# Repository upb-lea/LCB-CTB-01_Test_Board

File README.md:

# Test board LCB-CTB-01 for the LEA control board

This is the test board for the LEA control board LCB-CCB-01. It is used for testing an LCB-board to see if this works well. Please refer to the [LCB-CCB-01 repository](https://github.com/upb-lea/LCB-CCB-01_LEA_Control_Board) for a PCB and project overview.

Note, that you also need to install the `LEA KiCad Library` to view this PCB in this repository. To do this, follow the instructions mentioned [here](https://github.com/upb-lea/LCB-CCB-01_LEA_Control_Board/blob/main/README.md#downloading-this-project-and-folder-structure).

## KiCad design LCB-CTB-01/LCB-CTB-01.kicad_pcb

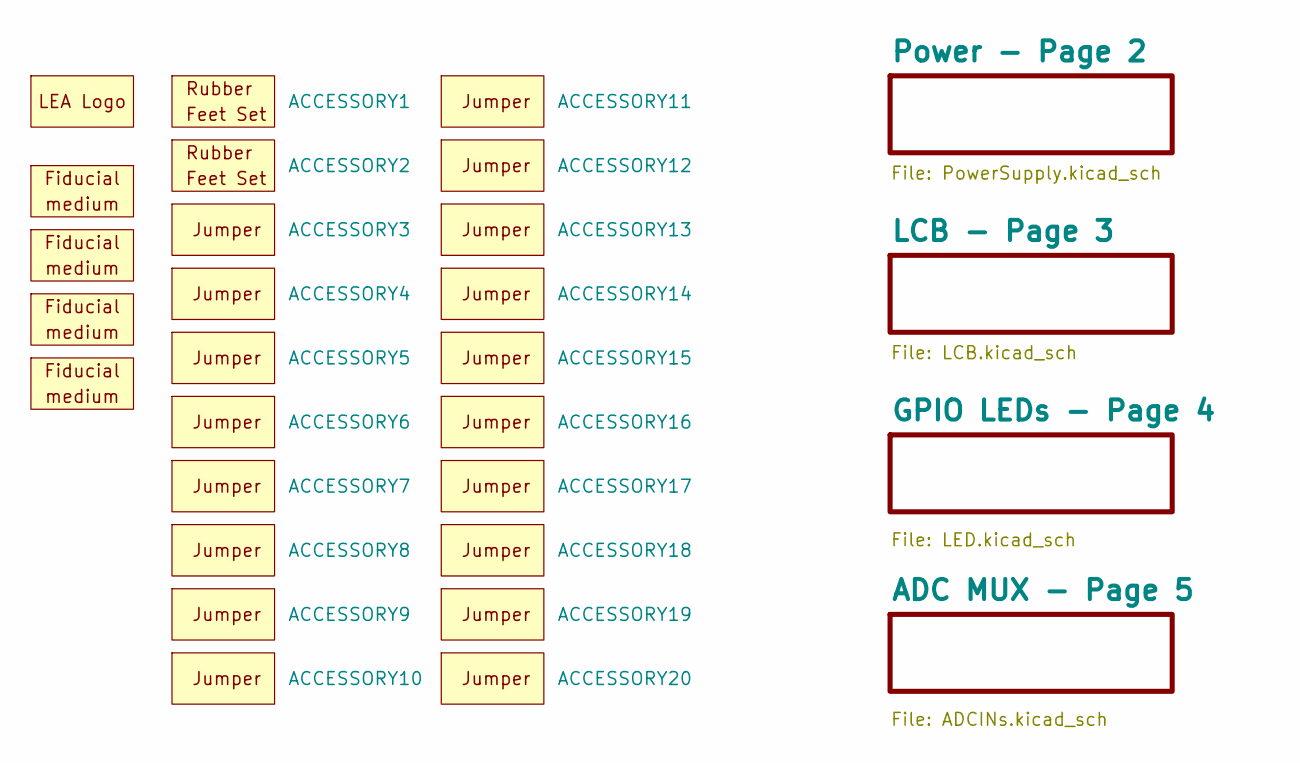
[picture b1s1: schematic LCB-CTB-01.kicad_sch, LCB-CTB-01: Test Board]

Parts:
ACCESSORY1, ACCESSORY2: ACCESSORY_rubber_feet; mouser# 485-550
ACCESSORY3, ACCESSORY4, ACCESSORY5, ACCESSORY6, ACCESSORY7, ACCESSORY8, ACCESSORY9, ACCESSORY10, ACCESSORY11, ACCESSORY12, ACCESSORY13, ACCESSORY14, ACCESSORY15, ACCESSORY16, ACCESSORY17, ACCESSORY18, ACCESSORY19, ACCESSORY20: ACCESSORY_jumper; mouser# 571-8815451
O1: SYM_LEA_Logo; SYM_lea_logo
O2, O3, O4, O5: Fiducial_medium; Fiducials_medium

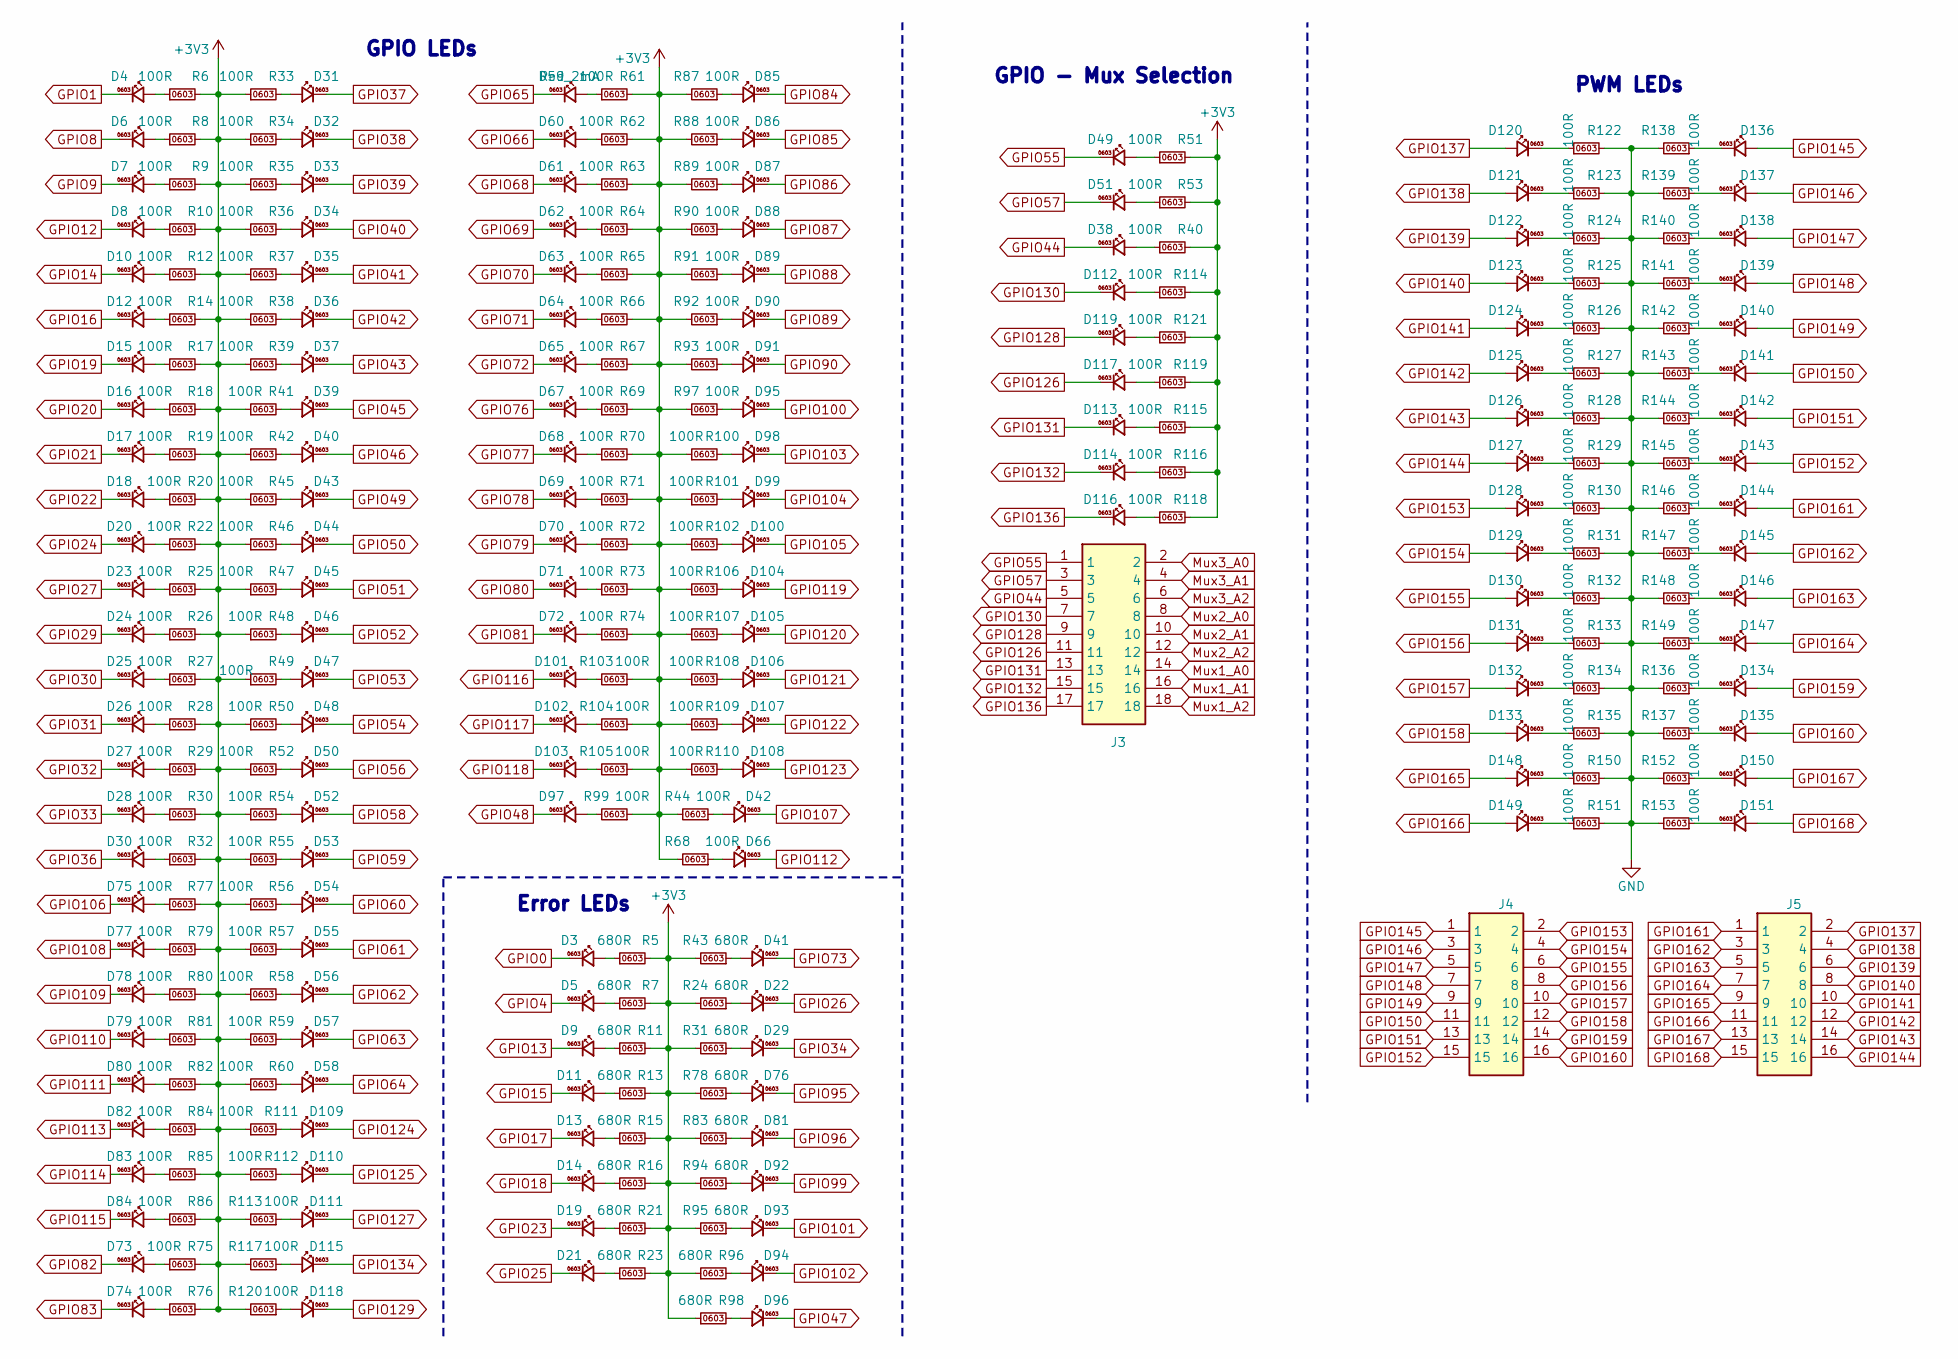
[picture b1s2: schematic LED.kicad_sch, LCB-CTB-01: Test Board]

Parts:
D3, D5, D9, D11, D13, D14, D19, D21, D22, D29, D41, D59, D76, D81, D92, D93, D94, D96: Red_2mA; LED_0603; mouser# 604-APHD1608LSURCK
D4, D6, D7, D8, D10, D12, D15, D16, D17, D18, D20, D23, D24, D25, D26, D27, D28, D30, D31, D32, D33, D34, D35, D36, D37, D38, D39, D40, D42, D43, D44, D45, D46, D47, D48, D49, D50, D51, D52, D53, D54, D55, D56, D57, D58, D60, D61, D62, D63, D64, D65, D66, D67, D68, D69, D70, D71, D72, D73, D74, D75, D77, D78, D79, D80, D82, D83, D84, D85, D86, D87, D88, D89, D90, D91, D95, D97, D98, D99, D100, D101, D102, D103, D104, D105, D106, D107, D108, D109, D110, D111, D112, D113, D114, D115, D116, D117, D118, D119, D120, D121, D122, D123, D124, D125, D126, D127, D128, D129, D130, D131, D132, D133, D134, D135, D136, D137, D138, D139, D140, D141, D142, D143, D144, D145, D146, D147, D148, D149, D150, D151: LED_0603_BLUE; LED_0603; mouser# 604-APHD1608LVBCD
J3: Conn_02x09_Male; mouser# 855-M20-9980946
J4, J5: Conn_02x08_Male; HDRV16W64P254_2X8_2032X508X914P; mouser# 855-M20-9980846
R5, R7, R11, R13, R15, R16, R21, R23, R24, R31, R43, R78, R83, R94, R95, R96, R98: 680R; R_0603; mouser# 71-CRCW0603680RFKEAC
R6, R8, R9, R10, R12, R14, R17, R18, R19, R20, R22, R25, R26, R27, R28, R29, R30, R32, R33, R34, R35, R36, R37, R38, R39, R40, R41, R42, R44, R45, R46, R47, R48, R49, R50, R51, R52, R53, R54, R55, R56, R57, R58, R59, R60, R61, R62, R63, R64, R65, R66, R67, R68, R69, R70, R71, R72, R73, R74, R75, R76, R77, R79, R80, R81, R82, R84, R85, R86, R87, R88, R89, R90, R91, R92, R93, R97, R99, R100, R101, R102, R103, R104, R105, R106, R107, R108, R109, R110, R111, R112, R113, R114, R115, R116, R117, R118, R119, R120, R121, R122, R123, R124, R125, R126, R127, R128, R129, R130, R131, R132, R133, R134, R135, R136, R137, R138, R139, R140, R141, R142, R143, R144, R145, R146, R147, R148, R149, R150, R151, R152, R153: 100R; R_0603; mouser# 71-CRCW0603100RFKEAC

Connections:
+3V3: R5.2, R6.2, R7.2, R8.2, R9.2, R10.2, R11.2, R12.2, R13.2, R14.2, R15.2, R16.2, R17.2, R18.2, R19.2, R20.2, R21.2, R22.2, R23.2, R24.2, R25.2, R26.2, R27.2, R28.2, R29.2, R30.2, R31.2, R32.2, R33.1, R34.1, R35.1, R36.1, R37.1, R38.1, R39.1, R40.2, R41.1, R42.1, R43.2, R44.2, R45.1, R46.1, R47.1, R48.1, R49.1, R50.1, R51.2, R52.1, R53.2, R54.1, R55.1, R56.1, R57.1, R58.1, R59.1, R60.1, R61.2, R62.2, R63.2, R64.2, R65.2, R66.2, R67.2, R68.2, R69.2, R70.2, R71.2, R72.2, R73.2, R74.2, R75.2, R76.2, R77.2, R78.2, R79.2, R80.2, R81.2, R82.2, R83.2, R84.2, R85.2, R86.2, R87.2, R88.2, R89.2, R90.2, R91.2, R92.2, R93.2, R94.2, R95.2, R96.1, R97.2, R98.1, R99.1, R100.1, R101.1, R102.1, R103.1, R104.1, R105.1, R106.1, R107.1, R108.1, R109.1, R110.1, R111.1, R112.1, R113.2, R114.2, R115.2, R116.2, R117.2, R118.2, R119.2, R120.2, R121.2; also elsewhere on the board
GND: R122.2, R123.2, R124.2, R125.2, R126.2, R127.2, R128.2, R129.2, R130.2, R131.2, R132.2, R133.2, R134.2, R135.2, R136.2, R137.2, R138.2, R139.2, R140.2, R141.2, R142.2, R143.2, R144.2, R145.2, R146.2, R147.2, R148.2, R149.2, R150.2, R151.2, R152.2, R153.2; also elsewhere on the board
GPIO0: D3.C; also elsewhere on the board
GPIO1: D4.C; also elsewhere on the board
GPIO4: D5.C; also elsewhere on the board
GPIO8: D6.C; also elsewhere on the board
GPIO9: D7.C; also elsewhere on the board
GPIO12: D8.C; also elsewhere on the board
GPIO13: D9.C; also elsewhere on the board
GPIO14: D10.C; also elsewhere on the board
GPIO15: D11.C; also elsewhere on the board
GPIO16: D12.C; also elsewhere on the board
GPIO17: D13.C; also elsewhere on the board
GPIO18: D14.C; also elsewhere on the board
GPIO19: D15.C; also elsewhere on the board
GPIO20: D16.C; also elsewhere on the board
GPIO21: D17.C; also elsewhere on the board
GPIO22: D18.C; also elsewhere on the board
GPIO23: D19.C; also elsewhere on the board
GPIO24: D20.C; also elsewhere on the board
GPIO25: D21.C; also elsewhere on the board
GPIO26: D22.C; also elsewhere on the board
GPIO27: D23.C; also elsewhere on the board
GPIO29: D24.C; also elsewhere on the board
GPIO30: D25.C; also elsewhere on the board
GPIO31: D26.C; also elsewhere on the board
GPIO32: D27.C; also elsewhere on the board
GPIO33: D28.C; also elsewhere on the board
GPIO34: D29.C; also elsewhere on the board
GPIO36: D30.C; also elsewhere on the board
GPIO37: D31.C; also elsewhere on the board
GPIO38: D32.C; also elsewhere on the board
GPIO39: D33.C; also elsewhere on the board
GPIO40: D34.C; also elsewhere on the board
GPIO41: D35.C; also elsewhere on the board
GPIO42: D36.C; also elsewhere on the board
GPIO43: D37.C; also elsewhere on the board
GPIO44: D38.C, J3.5; also elsewhere on the board
GPIO45: D39.C; also elsewhere on the board
GPIO46: D40.C; also elsewhere on the board
GPIO47: D96.C; also elsewhere on the board
GPIO48: D97.C; also elsewhere on the board
GPIO49: D43.C; also elsewhere on the board
GPIO50: D44.C; also elsewhere on the board
GPIO51: D45.C; also elsewhere on the board
GPIO52: D46.C; also elsewhere on the board
GPIO53: D47.C; also elsewhere on the board
GPIO54: D48.C; also elsewhere on the board
GPIO55: D49.C, J3.1; also elsewhere on the board
GPIO56: D50.C; also elsewhere on the board
GPIO57: D51.C, J3.3; also elsewhere on the board
GPIO58: D52.C; also elsewhere on the board
GPIO59: D53.C; also elsewhere on the board
GPIO60: D54.C; also elsewhere on the board
GPIO61: D55.C; also elsewhere on the board
GPIO62: D56.C; also elsewhere on the board
GPIO63: D57.C; also elsewhere on the board
GPIO64: D58.C; also elsewhere on the board
GPIO65: D59.C; also elsewhere on the board
GPIO66: D60.C; also elsewhere on the board
GPIO68: D61.C; also elsewhere on the board
GPIO69: D62.C; also elsewhere on the board
GPIO70: D63.C; also elsewhere on the board
GPIO71: D64.C; also elsewhere on the board
GPIO72: D65.C; also elsewhere on the board
GPIO73: D41.C; also elsewhere on the board
GPIO76: D67.C; also elsewhere on the board
GPIO77: D68.C; also elsewhere on the board
GPIO78: D69.C; also elsewhere on the board
GPIO79: D70.C; also elsewhere on the board
GPIO80: D71.C; also elsewhere on the board
GPIO81: D72.C; also elsewhere on the board
GPIO82: D73.C; also elsewhere on the board
GPIO83: D74.C; also elsewhere on the board
GPIO84: D85.C; also elsewhere on the board
GPIO85: D86.C; also elsewhere on the board
GPIO86: D87.C; also elsewhere on the board
GPIO87: D88.C; also elsewhere on the board
GPIO88: D89.C; also elsewhere on the board
GPIO89: D90.C; also elsewhere on the board
GPIO90: D91.C; also elsewhere on the board
GPIO95: D76.C; also elsewhere on the board
GPIO96: D81.C; also elsewhere on the board
GPIO99: D92.C; also elsewhere on the board
GPIO100: D95.C; also elsewhere on the board
GPIO101: D93.C; also elsewhere on the board
GPIO102: D94.C; also elsewhere on the board
GPIO103: D98.C; also elsewhere on the board
GPIO104: D99.C; also elsewhere on the board
GPIO105: D100.C; also elsewhere on the board
GPIO106: D75.C; also elsewhere on the board
GPIO107: D42.C; also elsewhere on the board
GPIO108: D77.C; also elsewhere on the board
GPIO109: D78.C; also elsewhere on the board
GPIO110: D79.C; also elsewhere on the board
GPIO111: D80.C; also elsewhere on the board
GPIO112: D66.C; also elsewhere on the board
GPIO113: D82.C; also elsewhere on the board
GPIO114: D83.C; also elsewhere on the board
GPIO115: D84.C; also elsewhere on the board
GPIO116: D101.C; also elsewhere on the board
GPIO117: D102.C; also elsewhere on the board
GPIO118: D103.C; also elsewhere on the board
GPIO119: D104.C; also elsewhere on the board
GPIO120: D105.C; also elsewhere on the board
GPIO121: D106.C; also elsewhere on the board
GPIO122: D107.C; also elsewhere on the board
GPIO123: D108.C; also elsewhere on the board
GPIO124: D109.C; also elsewhere on the board
GPIO125: D110.C; also elsewhere on the board
GPIO126: D117.C, J3.11; also elsewhere on the board
GPIO127: D111.C; also elsewhere on the board
GPIO128: D119.C, J3.9; also elsewhere on the board
GPIO129: D118.C; also elsewhere on the board
GPIO130: D112.C, J3.7; also elsewhere on the board
GPIO131: D113.C, J3.13; also elsewhere on the board
GPIO132: D114.C, J3.15; also elsewhere on the board
GPIO134: D115.C; also elsewhere on the board
GPIO136: D116.C, J3.17; also elsewhere on the board
GPIO137: D120.A, J5.2; also elsewhere on the board
GPIO138: D121.A, J5.4; also elsewhere on the board
GPIO139: D122.A, J5.6; also elsewhere on the board
GPIO140: D123.A, J5.8; also elsewhere on the board
GPIO141: D124.A, J5.10; also elsewhere on the board
GPIO142: D125.A, J5.12; also elsewhere on the board
GPIO143: D126.A, J5.14; also elsewhere on the board
GPIO144: D127.A, J5.16; also elsewhere on the board
GPIO145: D136.A, J4.1; also elsewhere on the board
GPIO146: D137.A, J4.3; also elsewhere on the board
GPIO147: D138.A, J4.5; also elsewhere on the board
GPIO148: D139.A, J4.7; also elsewhere on the board
GPIO149: D140.A, J4.9; also elsewhere on the board
GPIO150: D141.A, J4.11; also elsewhere on the board
GPIO151: D142.A, J4.13; also elsewhere on the board
GPIO152: D143.A, J4.15; also elsewhere on the board
GPIO153: D128.A, J4.2; also elsewhere on the board
GPIO154: D129.A, J4.4; also elsewhere on the board
GPIO155: D130.A, J4.6; also elsewhere on the board
GPIO156: D131.A, J4.8; also elsewhere on the board
GPIO157: D132.A, J4.10; also elsewhere on the board
GPIO158: D133.A, J4.12; also elsewhere on the board
GPIO159: D134.A, J4.14; also elsewhere on the board
GPIO160: D135.A, J4.16; also elsewhere on the board
GPIO161: D144.A, J5.1; also elsewhere on the board
GPIO162: D145.A, J5.3; also elsewhere on the board
GPIO163: D146.A, J5.5; also elsewhere on the board
GPIO164: D147.A, J5.7; also elsewhere on the board
GPIO165: D148.A, J5.9; also elsewhere on the board
GPIO166: D149.A, J5.11; also elsewhere on the board
GPIO167: D150.A, J5.13; also elsewhere on the board
GPIO168: D151.A, J5.15; also elsewhere on the board
Mux1_A0: J3.14; also elsewhere on the board
Mux1_A1: J3.16; also elsewhere on the board
Mux1_A2: J3.18; also elsewhere on the board
Mux2_A0: J3.8; also elsewhere on the board
Mux2_A1: J3.10; also elsewhere on the board
Mux2_A2: J3.12; also elsewhere on the board
Mux3_A0: J3.2; also elsewhere on the board
Mux3_A1: J3.4; also elsewhere on the board
Mux3_A2: J3.6; also elsewhere on the board
unnamed: D3.A, R5.1
unnamed: D4.A, R6.1
unnamed: D5.A, R7.1
unnamed: D6.A, R8.1
unnamed: D7.A, R9.1
unnamed: D8.A, R10.1
unnamed: D9.A, R11.1
unnamed: D10.A, R12.1
unnamed: D11.A, R13.1
unnamed: D12.A, R14.1
unnamed: D13.A, R15.1
unnamed: D14.A, R16.1
unnamed: D15.A, R17.1
unnamed: D16.A, R18.1
unnamed: D17.A, R19.1
unnamed: D18.A, R20.1
unnamed: D19.A, R21.1
unnamed: D20.A, R22.1
unnamed: D21.A, R23.1
unnamed: D22.A, R24.1
unnamed: D23.A, R25.1
unnamed: D24.A, R26.1
unnamed: D25.A, R27.1
unnamed: D26.A, R28.1
unnamed: D27.A, R29.1
unnamed: D28.A, R30.1
unnamed: D29.A, R31.1
unnamed: D30.A, R32.1
unnamed: D31.A, R33.2
unnamed: D32.A, R34.2
unnamed: D33.A, R35.2
unnamed: D34.A, R36.2
unnamed: D35.A, R37.2
unnamed: D36.A, R38.2
unnamed: D37.A, R39.2
unnamed: D38.A, R40.1
unnamed: D39.A, R41.2
unnamed: D40.A, R42.2
unnamed: D41.A, R43.1
unnamed: D42.A, R44.1
unnamed: D43.A, R45.2
unnamed: D44.A, R46.2
unnamed: D45.A, R47.2
unnamed: D46.A, R48.2
unnamed: D47.A, R49.2
unnamed: D48.A, R50.2
unnamed: D49.A, R51.1
unnamed: D50.A, R52.2
unnamed: D51.A, R53.1
unnamed: D52.A, R54.2
unnamed: D53.A, R55.2
unnamed: D54.A, R56.2
unnamed: D55.A, R57.2
unnamed: D56.A, R58.2
unnamed: D57.A, R59.2
unnamed: D58.A, R60.2
unnamed: D59.A, R61.1
unnamed: D60.A, R62.1
unnamed: D61.A, R63.1
unnamed: D62.A, R64.1
unnamed: D63.A, R65.1
unnamed: D64.A, R66.1
unnamed: D65.A, R67.1
unnamed: D66.A, R68.1
unnamed: D67.A, R69.1
unnamed: D68.A, R70.1
unnamed: D69.A, R71.1
unnamed: D70.A, R72.1
unnamed: D71.A, R73.1
unnamed: D72.A, R74.1
unnamed: D73.A, R75.1
unnamed: D74.A, R76.1
unnamed: D75.A, R77.1
unnamed: D76.A, R78.1
unnamed: D77.A, R79.1
unnamed: D78.A, R80.1
unnamed: D79.A, R81.1
unnamed: D80.A, R82.1
unnamed: D81.A, R83.1
unnamed: D82.A, R84.1
unnamed: D83.A, R85.1
unnamed: D84.A, R86.1
unnamed: D85.A, R87.1
unnamed: D86.A, R88.1
unnamed: D87.A, R89.1
unnamed: D88.A, R90.1
unnamed: D89.A, R91.1
unnamed: D90.A, R92.1
unnamed: D91.A, R93.1
unnamed: D92.A, R94.1
unnamed: D93.A, R95.1
unnamed: D94.A, R96.2
unnamed: D95.A, R97.1
unnamed: D96.A, R98.2
unnamed: D97.A, R99.2
unnamed: D98.A, R100.2
unnamed: D99.A, R101.2
unnamed: D100.A, R102.2
unnamed: D101.A, R103.2
unnamed: D102.A, R104.2
unnamed: D103.A, R105.2
unnamed: D104.A, R106.2
unnamed: D105.A, R107.2
unnamed: D106.A, R108.2
unnamed: D107.A, R109.2
unnamed: D108.A, R110.2
unnamed: D109.A, R111.2
unnamed: D110.A, R112.2
unnamed: D111.A, R113.1
unnamed: D112.A, R114.1
unnamed: D113.A, R115.1
unnamed: D114.A, R116.1
unnamed: D115.A, R117.1
unnamed: D116.A, R118.1
unnamed: D117.A, R119.1
unnamed: D118.A, R120.1
unnamed: D119.A, R121.1
unnamed: D120.C, R122.1
unnamed: D121.C, R123.1
unnamed: D122.C, R124.1
unnamed: D123.C, R125.1
unnamed: D124.C, R126.1
unnamed: D125.C, R127.1
unnamed: D126.C, R128.1
unnamed: D127.C, R129.1
unnamed: D128.C, R130.1
unnamed: D129.C, R131.1
unnamed: D130.C, R132.1
unnamed: D131.C, R133.1
unnamed: D132.C, R134.1
unnamed: D133.C, R135.1
unnamed: D134.C, R136.1
unnamed: D135.C, R137.1
unnamed: D136.C, R138.1
unnamed: D137.C, R139.1
unnamed: D138.C, R140.1
unnamed: D139.C, R141.1
unnamed: D140.C, R142.1
unnamed: D141.C, R143.1
unnamed: D142.C, R144.1
unnamed: D143.C, R145.1
unnamed: D144.C, R146.1
unnamed: D145.C, R147.1
unnamed: D146.C, R148.1
unnamed: D147.C, R149.1
unnamed: D148.C, R150.1
unnamed: D149.C, R151.1
unnamed: D150.C, R152.1
unnamed: D151.C, R153.1

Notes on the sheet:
PWM LEDs
GPIO - Mux Selection
Error LEDs
GPIO LEDs

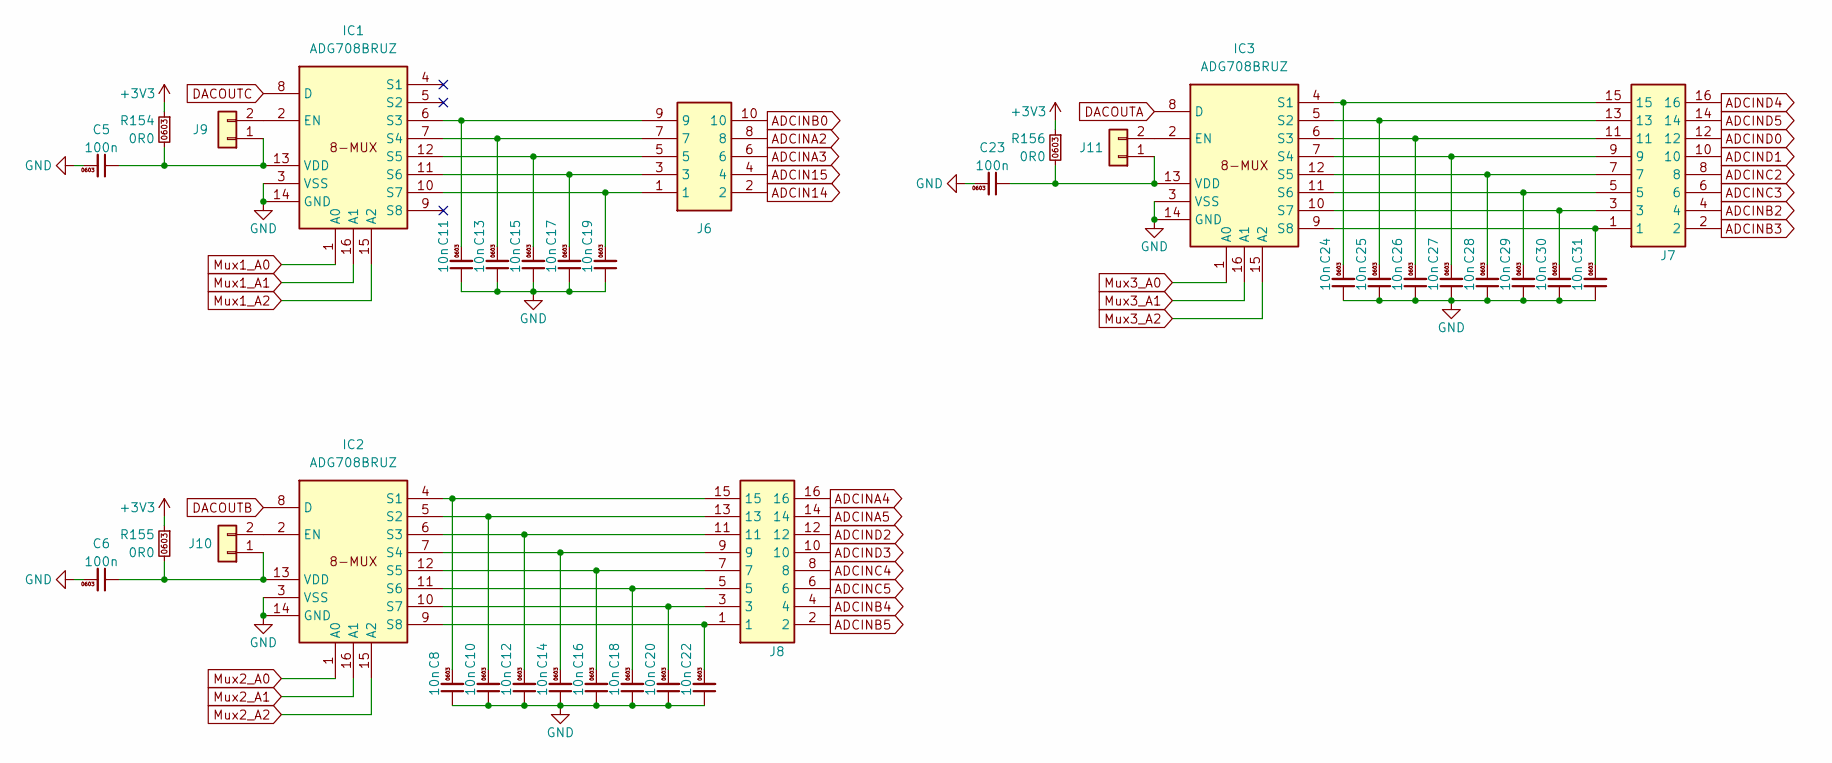
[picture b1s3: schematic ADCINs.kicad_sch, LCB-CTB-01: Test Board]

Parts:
C5, C6, C23: 100n; C_0603; mouser# 810-C1608X5R1H104K
C8, C10, C11, C12, C13, C14, C15, C16, C17, C18, C19, C20, C22, C24, C25, C26, C27, C28, C29, C30, C31: 10n; C_0603; mouser# 810-CGA3E2X7R1H103K
IC1, IC2, IC3: ADG708BRUZ; SOP65P640X120-16N; mouser# 584-ADG708BRUZ
J6: 10129381-910002BLF; Conn_02x05_Male; mouser# 649-1012938191002BLF
J7, J8: Conn_02x08_Male; HDRV16W64P254_2X8_2032X508X914P; mouser# 855-M20-9980846
J9, J10, J11: 01x02; PinHeader_1x02_P2.54mm_Vertical; mouser# 855-M20-9990245
R154, R155, R156: 0R0; R_0603; mouser# 71-CRCW06030000Z0EAC

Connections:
+3V3: R154.1, R155.1, R156.1; also elsewhere on the board
ADCIN14: J6.2; also elsewhere on the board
ADCIN15: J6.4; also elsewhere on the board
ADCINA2: J6.8; also elsewhere on the board
ADCINA3: J6.6; also elsewhere on the board
ADCINA4: J8.16; also elsewhere on the board
ADCINA5: J8.14; also elsewhere on the board
ADCINB0: J6.10; also elsewhere on the board
ADCINB2: J7.4; also elsewhere on the board
ADCINB3: J7.2; also elsewhere on the board
ADCINB4: J8.4; also elsewhere on the board
ADCINB5: J8.2; also elsewhere on the board
ADCINC2: J7.8; also elsewhere on the board
ADCINC3: J7.6; also elsewhere on the board
ADCINC4: J8.8; also elsewhere on the board
ADCINC5: J8.6; also elsewhere on the board
ADCIND0: J7.12; also elsewhere on the board
ADCIND1: J7.10; also elsewhere on the board
ADCIND2: J8.12; also elsewhere on the board
ADCIND3: J8.10; also elsewhere on the board
ADCIND4: J7.16; also elsewhere on the board
ADCIND5: J7.14; also elsewhere on the board
DACOUTA: IC3.8 (D); also elsewhere on the board
DACOUTB: IC2.8 (D); also elsewhere on the board
DACOUTC: IC1.8 (D); also elsewhere on the board
GND: C5.2, C6.2, C8.1, C10.1, C11.1, C12.1, C13.1, C14.1, C15.1, C16.1, C17.1, C18.1, C19.1, C20.1, C22.1, C23.2, C24.1, C25.1, C26.1, C27.1, C28.1, C29.1, C30.1, C31.1, IC1.3 (VSS), IC1.14 (GND), IC2.3 (VSS), IC2.14 (GND), IC3.3 (VSS), IC3.14 (GND); also elsewhere on the board
Mux1_A0: IC1.1 (A0); also elsewhere on the board
Mux1_A1: IC1.16 (A1); also elsewhere on the board
Mux1_A2: IC1.15 (A2); also elsewhere on the board
Mux2_A0: IC2.1 (A0); also elsewhere on the board
Mux2_A1: IC2.16 (A1); also elsewhere on the board
Mux2_A2: IC2.15 (A2); also elsewhere on the board
Mux3_A0: IC3.1 (A0); also elsewhere on the board
Mux3_A1: IC3.16 (A1); also elsewhere on the board
Mux3_A2: IC3.15 (A2); also elsewhere on the board
unnamed: IC1.2 (EN), J9.2
unnamed: C11.2, IC1.6 (S3), J6.9
unnamed: C13.2, IC1.7 (S4), J6.7
unnamed: C15.2, IC1.12 (S5), J6.5
unnamed: C17.2, IC1.11 (S6), J6.3
unnamed: C19.2, IC1.10 (S7), J6.1
unnamed: C5.1, IC1.13 (VDD), J9.1, R154.2
unnamed: IC2.2 (EN), J10.2
unnamed: C8.2, IC2.4 (S1), J8.15
unnamed: C10.2, IC2.5 (S2), J8.13
unnamed: C12.2, IC2.6 (S3), J8.11
unnamed: C14.2, IC2.7 (S4), J8.9
unnamed: C16.2, IC2.12 (S5), J8.7
unnamed: C18.2, IC2.11 (S6), J8.5
unnamed: C20.2, IC2.10 (S7), J8.3
unnamed: C22.2, IC2.9 (S8), J8.1
unnamed: C6.1, IC2.13 (VDD), J10.1, R155.2
unnamed: IC3.2 (EN), J11.2
unnamed: C24.2, IC3.4 (S1), J7.15
unnamed: C25.2, IC3.5 (S2), J7.13
unnamed: C26.2, IC3.6 (S3), J7.11
unnamed: C27.2, IC3.7 (S4), J7.9
unnamed: C28.2, IC3.12 (S5), J7.7
unnamed: C29.2, IC3.11 (S6), J7.5
unnamed: C30.2, IC3.10 (S7), J7.3
unnamed: C31.2, IC3.9 (S8), J7.1
unnamed: C23.1, IC3.13 (VDD), J11.1, R156.2

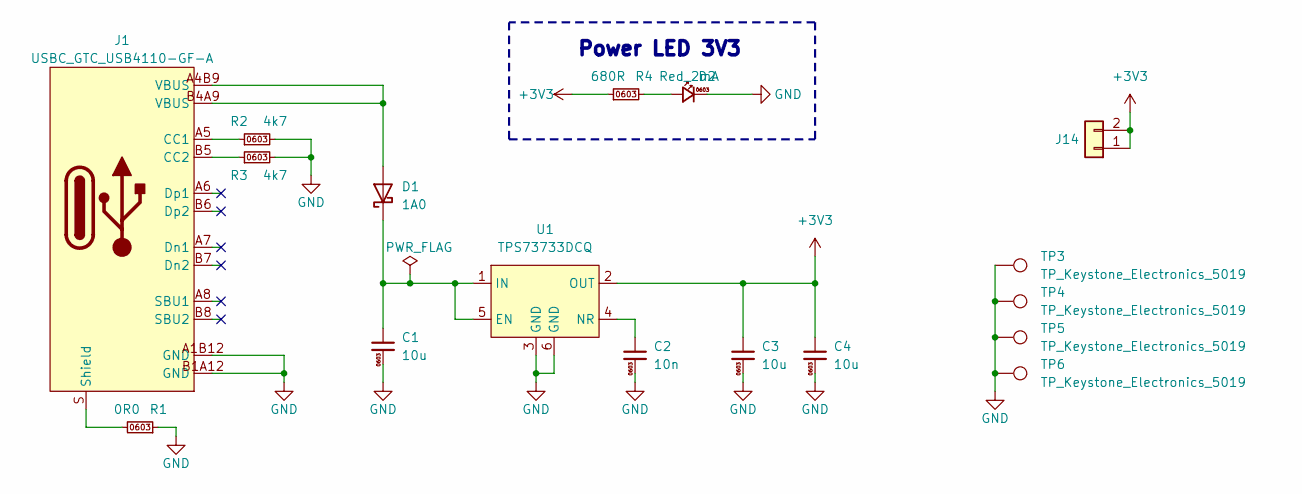
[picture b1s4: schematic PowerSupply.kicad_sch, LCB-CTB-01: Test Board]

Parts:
C1, C3, C4: 10u; C_0603; mouser# 81-GRM188R61E106KA3D
C2: 10n; C_0603; mouser# 810-CGA3E2X7R1H103K
D1: 1A0; SOD-323_Infineon; mouser# 726-BAS3010A-03WE6; Mouser No 726-BAS3010A-03WE6
D2: Red_2mA; LED_0603; mouser# 604-APHD1608LSURCK
J1: USBC_GTC_USB4110-GF-A; USB_C_GCT_USB4110-GF-A; mouser# 640-USB4110-GF-A; Mouser No 640-USB4110-GF-A
J14: 01x02; PinHeader_1x02_P2.54mm_Vertical; mouser# 855-M20-9990245
R1: 0R0; R_0603; mouser# 71-CRCW06030000Z0EAC
R2, R3: 4k7; R_0603; mouser# 71-CRCW06034K70FKEBC
R4: 680R; R_0603; mouser# 71-CRCW0603680RFKEAC
TP3, TP4, TP5, TP6: TP_Keystone_Electronics_5019; TestPoint_KeystoneElectronics5019; mouser# 534-5019
U1: TPS73733DCQ; SOT-223-6_TI; mouser# 595-TPS73733DCQG4; Mouser No. 595-TPS73733DCQG4

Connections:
+3V3: C3.1, C4.1, J14.1, J14.2, R4.1, U1.2 (OUT); also elsewhere on the board
GND: C1.2, C2.2, C3.2, C4.2, D2.C, J1.A1B12 (GND), J1.B1A12 (GND), R1.1, R2.2, R3.2, TP3.1 (TP), TP4.1 (TP), TP5.1 (TP), TP6.1 (TP), U1.3 (GND), U1.6 (GND); also elsewhere on the board
unnamed: D1.A, J1.A4B9 (VBUS), J1.B4A9 (VBUS)
unnamed: D2.A, R4.2
unnamed: J1.A5 (CC1), R2.1
unnamed: J1.B5 (CC2), R3.1
unnamed: J1.S (Shield), R1.2
unnamed: C1.1, D1.C, U1.1 (IN), U1.5 (EN)
unnamed: C2.1, U1.4 (NR)

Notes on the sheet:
Power LED 3V3
